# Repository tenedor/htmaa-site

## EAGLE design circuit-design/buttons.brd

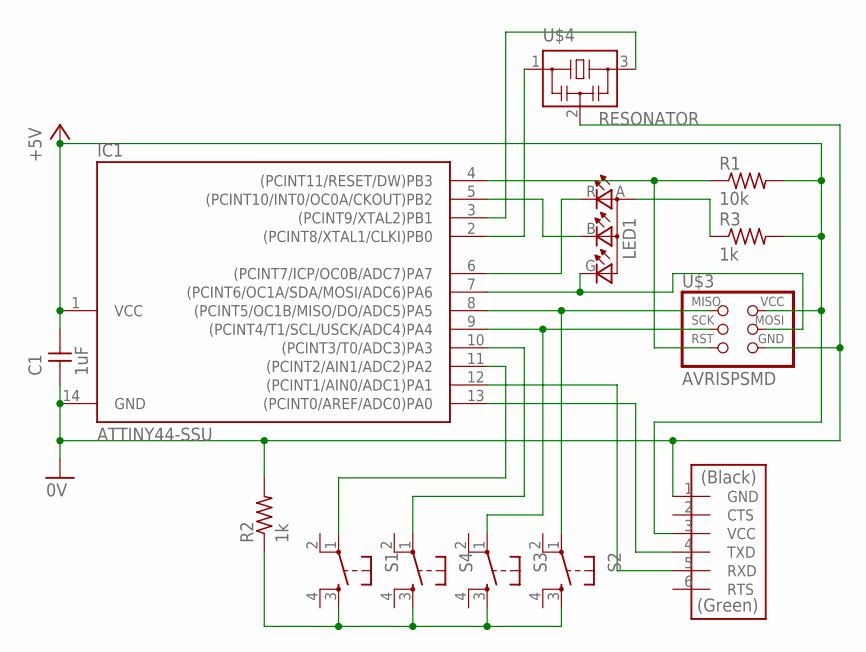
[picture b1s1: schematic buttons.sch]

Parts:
C1: 1uF; C1206FAB
IC1: ATTINY44-SSU; SOIC14
LED1: LEDRGBOLD; P-LCC-4-3
R1: 10k; R1206FAB
R2, R3: 1k; R1206FAB
S1, S2, S3, S4: 6MM_SWITCH6MM_SWITCH; 6MM_SWITCH
U$2: FTDI-SMD-HEADER; 1X06SMD
U$3: AVRISPSMD; 2X03SMD
U$4: RESONATOR; EFOBM

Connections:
0V: C1.1, IC1.14 (GND), R2.2, U$2.1 (GND), U$3.6 (GND), U$4.2
+5V: C1.2, IC1.1 (VCC), R1.2, R3.2, U$2.3 (VCC), U$3.2 (VCC)
unnamed: IC1.3 ((PCINT9/XTAL2)PB1), U$4.3
unnamed: IC1.2 ((PCINT8/XTAL1/CLKI)PB0), U$4.1
unnamed: IC1.9 ((PCINT4/T1/SCL/USCK/ADC4)PA4), S3.1, U$3.3 (SCK)
unnamed: IC1.8 ((PCINT5/OC1B/MISO/DO/ADC5)PA5), S2.1, U$3.1 (MISO)
unnamed: IC1.7 ((PCINT6/OC1A/SDA/MOSI/ADC6)PA6), LED1.G (CGREEN), U$3.4 (MOSI)
unnamed: IC1.4 ((PCINT11/RESET/DW)PB3), R1.1, U$3.5 (RST)
unnamed: IC1.5 ((PCINT10/INT0/OC0A/CKOUT)PB2), LED1.B (CBLUE)
unnamed: IC1.13 ((PCINT0/AREF/ADC0)PA0), U$2.4 (TXD)
unnamed: IC1.12 ((PCINT1/AIN0/ADC1)PA1), U$2.5 (RXD)
unnamed: IC1.6 ((PCINT7/ICP/OC0B/ADC7)PA7), LED1.R (CRED)
unnamed: LED1.A (A2), R3.1
unnamed: IC1.10 ((PCINT3/T0/ADC3)PA3), S4.1
unnamed: IC1.11 ((PCINT2/AIN1/ADC2)PA2), S1.1
unnamed: R2.1, S1.3 (S), S2.3 (S), S3.3 (S), S4.3 (S)

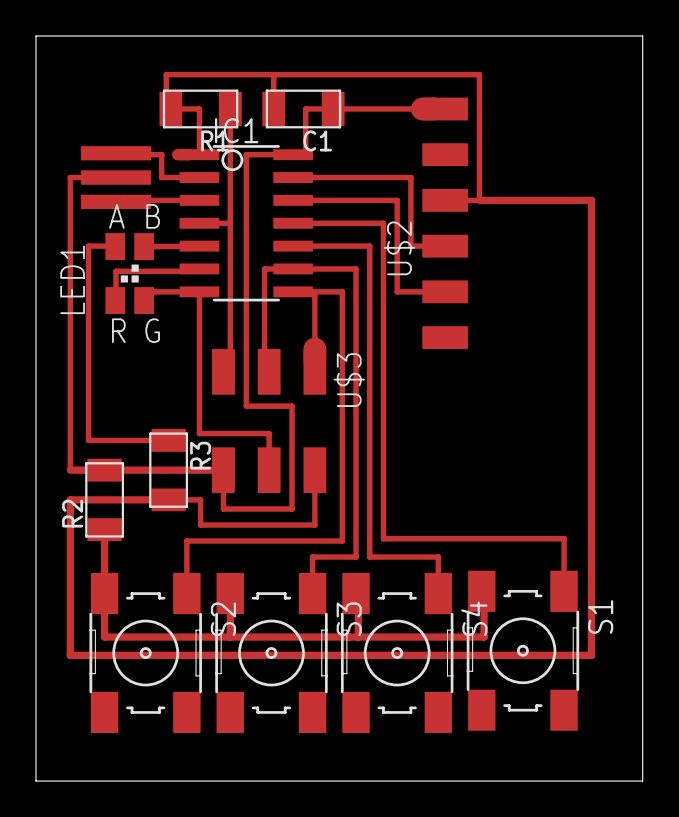
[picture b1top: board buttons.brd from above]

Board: 2 copper layers, 33.7 x 41.4 mm, 13 parts (0 on the bottom side), 16 nets.

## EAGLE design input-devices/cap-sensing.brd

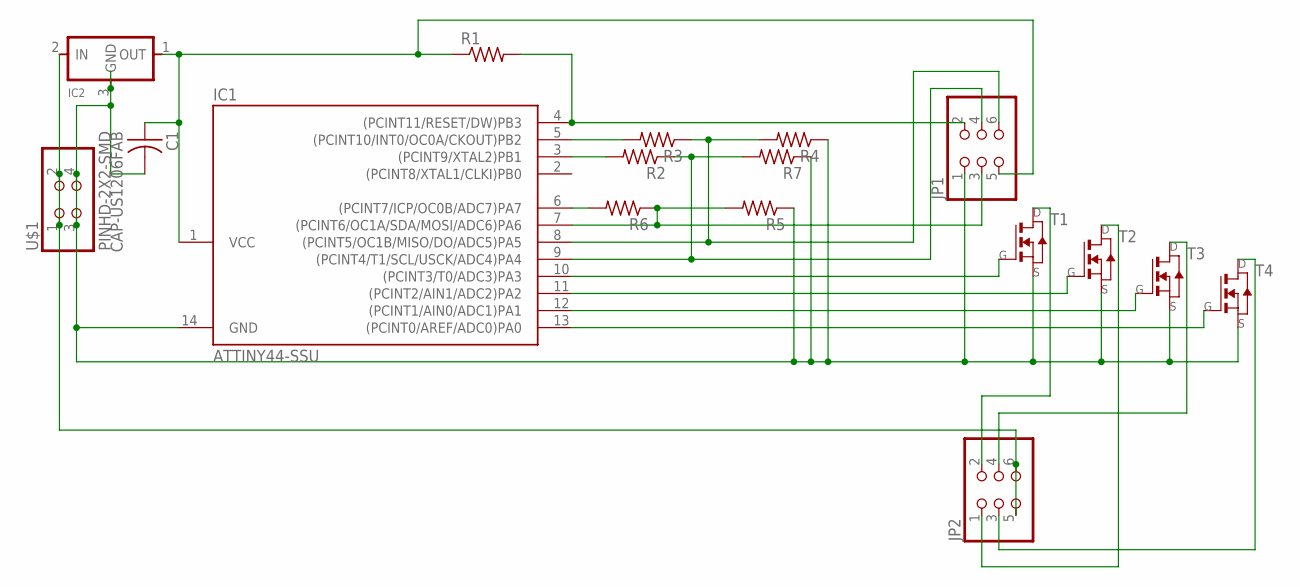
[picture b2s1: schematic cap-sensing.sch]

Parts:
C1: CAP-US1206FAB; C1206FAB
IC1: ATTINY44-SSU; SOIC14
IC2: REGULATORSOT23; SOT23
JP1, JP2: PINHD-2X3-SMD; 2X03SMD
R1, R2, R3, R4, R5, R6, R7: RES-US1206FAB; R1206FAB
T1, T2, T3, T4: NMOSFETSOT23; SOT-23
U$1: PINHD-2X2-SMD; 2X02SMD

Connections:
unnamed: IC1.5 ((PCINT10/INT0/OC0A/CKOUT)PB2), R3.2
unnamed: C1.2, IC1.14 (GND), IC2.3 (GND), JP1.1, R4.1, R5.1, R7.1, T1.2 (S), T2.2 (S), T3.2 (S), T4.2 (S), U$1.3, U$1.4
unnamed: C1.1, IC1.1 (VCC), IC2.1 (OUT), JP1.5, R1.1
unnamed: IC1.4 ((PCINT11/RESET/DW)PB3), JP1.2, R1.2
unnamed: IC1.9 ((PCINT4/T1/SCL/USCK/ADC4)PA4), JP1.4, R2.1, R7.2
unnamed: IC1.7 ((PCINT6/OC1A/SDA/MOSI/ADC6)PA6), JP1.3, R5.2, R6.1
unnamed: IC1.10 ((PCINT3/T0/ADC3)PA3), T1.3 (G)
unnamed: IC1.11 ((PCINT2/AIN1/ADC2)PA2), T2.3 (G)
unnamed: IC1.12 ((PCINT1/AIN0/ADC1)PA1), T3.3 (G)
unnamed: IC1.13 ((PCINT0/AREF/ADC0)PA0), T4.3 (G)
unnamed: JP2.2, T1.1 (D)
unnamed: JP2.4, T3.1 (D)
unnamed: JP2.1, T2.1 (D)
unnamed: JP2.3, T4.1 (D)
unnamed: IC2.2 (IN), JP2.5, JP2.6, U$1.1, U$1.2
unnamed: IC1.3 ((PCINT9/XTAL2)PB1), R2.2
unnamed: IC1.6 ((PCINT7/ICP/OC0B/ADC7)PA7), R6.2
unnamed: IC1.8 ((PCINT5/OC1B/MISO/DO/ADC5)PA5), JP1.6, R3.1, R4.2

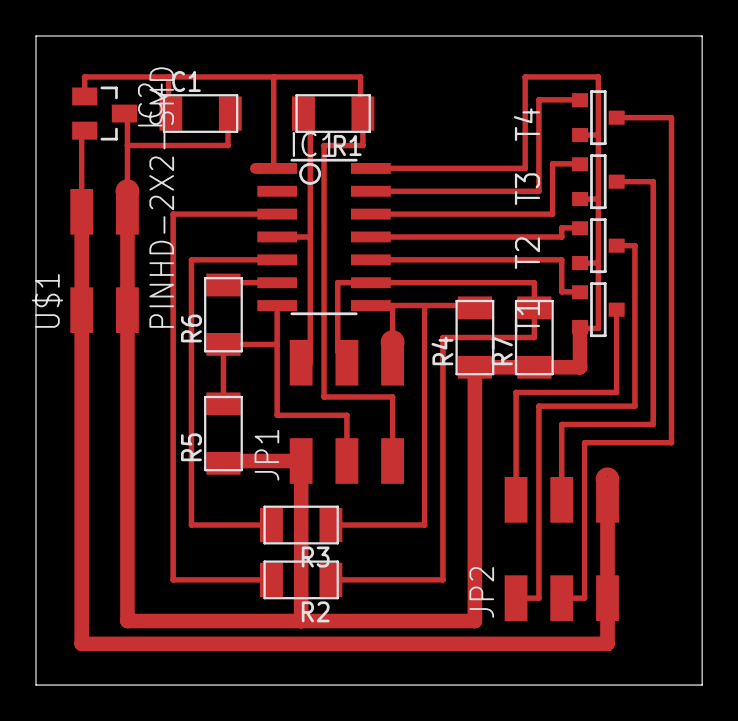
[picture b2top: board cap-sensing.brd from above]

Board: 2 copper layers, 37.0 x 36.1 mm, 17 parts (0 on the bottom side), 18 nets.

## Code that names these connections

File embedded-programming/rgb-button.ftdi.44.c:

//
// rgb-button.ftdi.44.c
//
// 115200 baud FTDI character echo, with flash string
//
// set lfuse to 0x7E for 20 MHz xtal
//
// Daniel Windham
// 11/04/15
//
// adapted from
// Neil Gershenfeld
// 12/8/10
//
// (c) Massachusetts Institute of Technology 2010
// This work may be reproduced, modified, distributed,
// performed, and displayed for any purpose. Copyright is
// retained and must be preserved. The work is provided
// as is; no warranty is provided, and users accept all 
// liability.
//

#include <avr/io.h>
#include <util/delay.h>
#include <avr/pgmspace.h>

#define output(directions,pin) (directions |= pin) // set port direction for output
#define input(directions,pin) (directions &= ~pin) // set port direction for input
#define pullup(port,pin) (port |= pin) // set internal pullup on input pin
#define set(port,pin) (port |= pin) // set port pin
#define clear(port,pin) (port &= (~pin)) // clear port pin
#define pin_test(pins,pin) (pins & pin) // test for port pin

#define led_r_direction DDRB
#define led_r_port PORTB
#define led_r_pin (1 << PB2)

#define led_g_direction DDRA
#define led_g_port PORTA
#define led_g_pin (1 << PA6)

#define led_b_direction DDRA
#define led_b_port PORTA
#define led_b_pin (1 << PA7)

#define buttons_direction DDRA
#define buttons_port PINA
#define buttons_pins PINA
#define button_0_pin (1 << PA5)
#define button_1_pin (1 << PA4)
#define button_2_pin (1 << PA3)
#define button_3_pin (1 << PA2)

void set_rgb_pulse_rates(int button_states[4], int rgb_pulses_per_ms[3]) {
  rgb_pulses_per_ms[0] = 0;
  rgb_pulses_per_ms[1] = 0;
  rgb_pulses_per_ms[2] = 0;
  if (button_states[0]) {
    rgb_pulses_per_ms[0] += 20;
    rgb_pulses_per_ms[1] += 0;
    rgb_pulses_per_ms[2] += 0;
  }
  if (button_states[1]) {
    rgb_pulses_per_ms[0] += 0;
    rgb_pulses_per_ms[1] += 50;
    rgb_pulses_per_ms[2] += 0;
  }
  if (button_states[2]) {
    rgb_pulses_per_ms[0] += 0;
    rgb_pulses_per_ms[1] += 0;
    rgb_pulses_per_ms[2] += 50;
  }
  if (button_states[3]) {
    if (button_states[0] || button_states[1] || button_states[2]) {
      rgb_pulses_per_ms[0] *= 2;
      rgb_pulses_per_ms[1] *= 2;
      rgb_pulses_per_ms[2] *= 2;
    } else {
      rgb_pulses_per_ms[0] += 10;
      rgb_pulses_per_ms[1] += 25;
      rgb_pulses_per_ms[2] += 25;
    }
  }
}

int main(void) {
  // set clock divider to /1
  CLKPR = (1 << CLKPCE);
  CLKPR = (0 << CLKPS3) | (0 << CLKPS2) | (0 << CLKPS1) | (0 << CLKPS0);

  // initialize rgb output pins
  set(led_r_port, led_r_pin);
  set(led_g_port, led_g_pin);
  set(led_b_port, led_b_pin);
  output(led_r_direction, led_r_pin);
  output(led_g_direction, led_g_pin);
  output(led_b_direction, led_b_pin);

  input(buttons_direction, button_0_pin);
  input(buttons_direction, button_1_pin);
  input(buttons_direction, button_2_pin);
  input(buttons_direction, button_3_pin);
  pullup(buttons_port, button_0_pin);
  pullup(buttons_port, button_1_pin);
  pullup(buttons_port, button_2_pin);
  pullup(buttons_port, button_3_pin);

  unsigned int elapsed_us = 0;
  int button_polls_per_second = 10;
  int button_states[4] = {0, 0, 0, 0};
  int rgb_pulses_per_ms[3] = {0, 0, 0};

  while (1) {
    _delay_us(1);
    elapsed_us++;

    // poll button state
    if (elapsed_us % 1000 < button_polls_per_second) {
      if (!pin_test(buttons_pins, button_0_pin)) {
        button_states[0] = 10;
      } else if (button_states[0]) {
        button_states[0]--;
      }
      if (!pin_test(buttons_pins, button_1_pin)) {
        button_states[1] = 10;
      } else if (button_states[1]) {
        button_states[1]--;
      }
      if (!pin_test(buttons_pins, button_2_pin)) {
        button_states[2] = 10;
      } else if (button_states[2]) {
        button_states[2]--;
      }
      if (!pin_test(buttons_pins, button_3_pin)) {
        button_states[3] = 10;
      } else if (button_states[3]) {
        button_states[3]--;
      }
    }

    // calculate rgb values
    set_rgb_pulse_rates(button_states, rgb_pulses_per_ms);

    // update red led
    if (elapsed_us % 1000 < rgb_pulses_per_ms[0]) {
      clear(led_r_port, led_r_pin);
    } else {
      set(led_r_port, led_r_pin);
    }
    // update green led
    if (elapsed_us % 1000 < rgb_pulses_per_ms[1]) {
      clear(led_g_port, led_g_pin);
    } else {
      set(led_g_port, led_g_pin);
    }
    // update blue led
    if (elapsed_us % 1000 < rgb_pulses_per_ms[2]) {
      clear(led_b_port, led_b_pin);
    } else {
      set(led_b_port, led_b_pin);
    }
  }
}

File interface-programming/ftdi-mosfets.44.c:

//
// ftdi-mosfets.44.c
//
// ftdi communication and mosfet power switches
//
// Daniel Windham
// 11/25/15
//
// adapted from
// Neil Gershenfeld
// 11/14/10
//
// (c) Massachusetts Institute of Technology 2010
// This work may be reproduced, modified, distributed,
// performed, and displayed for any purpose. Copyright is
// retained and must be preserved. The work is provided
// as is; no warranty is provided, and users accept all 
// liability.
//

#include <avr/io.h>
#include <util/delay.h>
#include <avr/pgmspace.h>

#define output(directions,pin) (directions |= pin) // set port direction for output
#define set(port,pin) (port |= pin) // set port pin
#define clear(port,pin) (port &= (~pin)) // clear port pin
#define pin_test(pins,pin) (pins & pin) // test for port pin
#define bit_test(byte,bit) (byte & (1 << bit)) // test for bit set
#define bit_delay_time 103 // bit delay for 9600 with overhead
#define bit_delay() _delay_us(bit_delay_time) // RS232 bit delay
#define half_bit_delay() _delay_us(bit_delay_time/2) // RS232 half bit delay
#define char_delay() _delay_ms(10) // char delay

#define serial_port PORTA
#define serial_direction DDRA
#define serial_pins PINA
#define serial_pin_in (1 << PA6)
#define serial_pin_out (1 << PA7)

#define mosfet_switch_port PORTA // mosfet switch port
#define mosfet_switch_direction DDRA // mosfet switch direction
#define mosfet_switch_0 (1 << PA4) // mosfet switch pins
#define mosfet_switch_1 (1 << PA3) // "
#define mosfet_switch_2 (1 << PA2) // "
#define mosfet_switch_3 (1 << PA1) // "
#define laser_mosfet_switch (1 << PA0) // laser mosfet switch pin

void get_char(volatile unsigned char *pins, unsigned char pin, char *rxbyte) {
  //
  // read character into rxbyte on pins pin
  //    assumes line driver (inverts bits)
  //
  *rxbyte = 0;
  while (pin_test(*pins,pin))
    //
    // wait for start bit
    //
    ;
  //
  // delay to middle of first data bit
  //
  half_bit_delay();
  bit_delay();
  //
  // unrolled loop to read data bits
  //
  if pin_test(*pins,pin)
    *rxbyte |= (1 << 0);
  else
    *rxbyte |= (0 << 0);
  bit_delay();
  if pin_test(*pins,pin)
    *rxbyte |= (1 << 1);
  else
    *rxbyte |= (0 << 1);
  bit_delay();
  if pin_test(*pins,pin)
    *rxbyte |= (1 << 2);
  else
    *rxbyte |= (0 << 2);
  bit_delay();
  if pin_test(*pins,pin)
    *rxbyte |= (1 << 3);
  else
    *rxbyte |= (0 << 3);
  bit_delay();
  if pin_test(*pins,pin)
    *rxbyte |= (1 << 4);
  else
    *rxbyte |= (0 << 4);
  bit_delay();
  if pin_test(*pins,pin)
    *rxbyte |= (1 << 5);
  else
    *rxbyte |= (0 << 5);
  bit_delay();
  if pin_test(*pins,pin)
    *rxbyte |= (1 << 6);
  else
    *rxbyte |= (0 << 6);
  bit_delay();
  if pin_test(*pins,pin)
    *rxbyte |= (1 << 7);
  else
    *rxbyte |= (0 << 7);
  //
  // wait for stop bit
  //
  bit_delay();
  half_bit_delay();
}

void put_char(volatile unsigned char *port, unsigned char pin, char txchar) {
  //
  // send character in txchar on port pin
  //    assumes line driver (inverts bits)
  //
  // start bit
  //
  clear(*port,pin);
  bit_delay();
  //
  // unrolled loop to write data bits
  //
  if bit_test(txchar,0)
    set(*port,pin);
  else
    clear(*port,pin);
  bit_delay();
  if bit_test(txchar,1)
    set(*port,pin);
  else
    clear(*port,pin);
  bit_delay();
  if bit_test(txchar,2)
    set(*port,pin);
  else
    clear(*port,pin);
  bit_delay();
  if bit_test(txchar,3)
    set(*port,pin);
  else
    clear(*port,pin);
  bit_delay();
  if bit_test(txchar,4)
    set(*port,pin);
  else
    clear(*port,pin);
  bit_delay();
  if bit_test(txchar,5)
    set(*port,pin);
  else
    clear(*port,pin);
  bit_delay();
  if bit_test(txchar,6)
    set(*port,pin);
  else
    clear(*port,pin);
  bit_delay();
  if bit_test(txchar,7)
    set(*port,pin);
  else
    clear(*port,pin);
  bit_delay();
  //
  // stop bit
  //
  set(*port,pin);
  bit_delay();
  //
  // char delay
  //
  bit_delay();
}

void put_string(volatile unsigned char *port, unsigned char pin, char *str) {
  //
  // print a null-terminated string
  //
  static int index;
  index = 0;
  do {
    put_char(port, pin, str[index]);
    ++index;
  } while (str[index] != 0);
}

int main(void) {
  // set clock divider to /1
  CLKPR = (1 << CLKPCE);
  CLKPR = (0 << CLKPS3) | (0 << CLKPS2) | (0 << CLKPS1) | (0 << CLKPS0);

  // initialize mosfet pins
  clear(mosfet_switch_port, mosfet_switch_0);
  clear(mosfet_switch_port, mosfet_switch_1);
  clear(mosfet_switch_port, mosfet_switch_2);
  clear(mosfet_switch_port, mosfet_switch_3);
  output(mosfet_switch_direction, mosfet_switch_0);
  output(mosfet_switch_direction, mosfet_switch_1);
  output(mosfet_switch_direction, mosfet_switch_2);
  output(mosfet_switch_direction, mosfet_switch_3);

  // initialize laser-mosfet pin
  clear(mosfet_switch_port, laser_mosfet_switch);
  output(mosfet_switch_direction, laser_mosfet_switch);

  // initialize output pins
  set(serial_port, serial_pin_out);
  output(serial_direction, serial_pin_out);

  char chr;
  char chr2 = 'a';

  while (1) {
    get_char(&serial_pins, serial_pin_in, &chr);
    if (chr == 'a') {
      set(mosfet_switch_port, laser_mosfet_switch);
    } else if (chr == 'b') {
      clear(mosfet_switch_port, laser_mosfet_switch);
      put_char(&serial_port, serial_pin_out, chr2);
      // increment chr2, staying inside the ascii printable character space
      chr2++;
      if (chr2 > 126) {
        chr2 = 33;
      }
    }
  }
}

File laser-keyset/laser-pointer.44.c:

//
// laser-pointer.44.c
//
// button-controlled laser pointer and ftdi communication
//
// Daniel Windham
// 12/12/15
//
// adapted from
// Neil Gershenfeld
// 11/14/10
//
// (c) Massachusetts Institute of Technology 2010
// This work may be reproduced, modified, distributed,
// performed, and displayed for any purpose. Copyright is
// retained and must be preserved. The work is provided
// as is; no warranty is provided, and users accept all 
// liability.
//

#include <avr/io.h>
#include <util/delay.h>
#include <avr/pgmspace.h>

#define output(directions,pin) (directions |= pin) // set port direction for output
#define input(directions,pin) (directions &= ~pin) // set port direction for input
#define pullup(port,pin) (port |= pin) // set internal pullup on input pin
#define set(port,pin) (port |= pin) // set port pin
#define clear(port,pin) (port &= (~pin)) // clear port pin
#define pin_test(pins,pin) (pins & pin) // test for port pin
#define bit_test(byte,bit) (byte & (1 << bit)) // test for bit set
#define bit_delay_time 103 // bit delay for 9600 with overhead
#define bit_delay() _delay_us(bit_delay_time) // RS232 bit delay
#define half_bit_delay() _delay_us(bit_delay_time/2) // RS232 half bit delay
#define char_delay() _delay_ms(10) // char delay

#define serial_port PORTB
#define serial_direction DDRB
#define serial_pins PINB
#define serial_pin_in (1 << PB1)
#define serial_pin_out (1 << PB0)

#define laser_port PORTA // laser switch port
#define laser_direction DDRA // laser switch direction
#define laser_pin (1 << PA0) // laser mosfet switch pin

#define buttons_port PORTA // buttons port
#define buttons_pins PINA // buttons pin
#define buttons_direction DDRA // buttons direction
#define laser_button_pin (1 << PA1) // laser button pin
#define button_0_pin (1 << PA2) // general button pins
#define button_1_pin (1 << PA3) // "
#define button_2_pin (1 << PA4) // "

void get_char(volatile unsigned char *pins, unsigned char pin, char *rxbyte) {
  //
  // read character into rxbyte on pins pin
  //    assumes line driver (inverts bits)
  //
  *rxbyte = 0;
  while (pin_test(*pins,pin))
    //
    // wait for start bit
    //
    ;
  //
  // delay to middle of first data bit
  //
  half_bit_delay();
  bit_delay();
  //
  // unrolled loop to read data bits
  //
  if pin_test(*pins,pin)
    *rxbyte |= (1 << 0);
  else
    *rxbyte |= (0 << 0);
  bit_delay();
  if pin_test(*pins,pin)
    *rxbyte |= (1 << 1);
  else
    *rxbyte |= (0 << 1);
  bit_delay();
  if pin_test(*pins,pin)
    *rxbyte |= (1 << 2);
  else
    *rxbyte |= (0 << 2);
  bit_delay();
  if pin_test(*pins,pin)
    *rxbyte |= (1 << 3);
  else
    *rxbyte |= (0 << 3);
  bit_delay();
  if pin_test(*pins,pin)
    *rxbyte |= (1 << 4);
  else
    *rxbyte |= (0 << 4);
  bit_delay();
  if pin_test(*pins,pin)
    *rxbyte |= (1 << 5);
  else
    *rxbyte |= (0 << 5);
  bit_delay();
  if pin_test(*pins,pin)
    *rxbyte |= (1 << 6);
  else
    *rxbyte |= (0 << 6);
  bit_delay();
  if pin_test(*pins,pin)
    *rxbyte |= (1 << 7);
  else
    *rxbyte |= (0 << 7);
  //
  // wait for stop bit
  //
  bit_delay();
  half_bit_delay();
}

void put_char(volatile unsigned char *port, unsigned char pin, char txchar) {
  //
  // send character in txchar on port pin
  //    assumes line driver (inverts bits)
  //
  // start bit
  //
  clear(*port,pin);
  bit_delay();
  //
  // unrolled loop to write data bits
  //
  if bit_test(txchar,0)
    set(*port,pin);
  else
    clear(*port,pin);
  bit_delay();
  if bit_test(txchar,1)
    set(*port,pin);
  else
    clear(*port,pin);
  bit_delay();
  if bit_test(txchar,2)
    set(*port,pin);
  else
    clear(*port,pin);
  bit_delay();
  if bit_test(txchar,3)
    set(*port,pin);
  else
    clear(*port,pin);
  bit_delay();
  if bit_test(txchar,4)
    set(*port,pin);
  else
    clear(*port,pin);
  bit_delay();
  if bit_test(txchar,5)
    set(*port,pin);
  else
    clear(*port,pin);
  bit_delay();
  if bit_test(txchar,6)
    set(*port,pin);
  else
    clear(*port,pin);
  bit_delay();
  if bit_test(txchar,7)
    set(*port,pin);
  else
    clear(*port,pin);
  bit_delay();
  //
  // stop bit
  //
  set(*port,pin);
  bit_delay();
  //
  // char delay
  //
  bit_delay();
}

void put_string(volatile unsigned char *port, unsigned char pin, char *str) {
  //
  // print a null-terminated string
  //
  static int index;
  index = 0;
  do {
    put_char(port, pin, str[index]);
    ++index;
  } while (str[index] != 0);
}

int main(void) {
  // set clock divider to /1
  CLKPR = (1 << CLKPCE);
  CLKPR = (0 << CLKPS3) | (0 << CLKPS2) | (0 << CLKPS1) | (0 << CLKPS0);

  // initialize laser pin
  set(laser_port, laser_pin);
  output(laser_direction, laser_pin);

  // initialize button pins
  input(buttons_direction, laser_button_pin);
  input(buttons_direction, button_0_pin);
  input(buttons_direction, button_1_pin);
  input(buttons_direction, button_2_pin);
  pullup(buttons_port, laser_button_pin);
  pullup(buttons_port, button_0_pin);
  pullup(buttons_port, button_1_pin);
  pullup(buttons_port, button_2_pin);

  // initialize serial pins
  set(serial_port, serial_pin_out);
  output(serial_direction, serial_pin_out);

  char buttons_state;

  while (1) {
    buttons_state = 0;

    // poll button states
    if (!pin_test(buttons_pins, button_0_pin)) {
      buttons_state |= 1 << 0;
    }
    if (!pin_test(buttons_pins, button_1_pin)) {
      buttons_state |= 1 << 1;
    }
    if (!pin_test(buttons_pins, button_2_pin)) {
      buttons_state |= 1 << 2;
    }

    // poll laser button state
    if (!pin_test(buttons_pins, laser_button_pin)) {
      buttons_state |= 1 << 3;
      set(laser_port, laser_pin);
    } else {
      clear(laser_port, laser_pin);
    }

    put_char(&serial_port, serial_pin_out, buttons_state);
  }
}

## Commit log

2015-10-24 2015-10-24 checkpoint
2016-08-08 2015-12-15 final website
2016-08-08 add imgs
2016-08-08 add group project page & fix img links
2016-08-08 add libs
2016-08-08 add link to original MAS.863-hosted site
2016-08-08 set link to external MAS.863 website
2016-08-08 add html, css, and sb files
